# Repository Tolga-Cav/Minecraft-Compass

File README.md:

# Minecraft-Compass
3D printed functioning Minecraft Compass

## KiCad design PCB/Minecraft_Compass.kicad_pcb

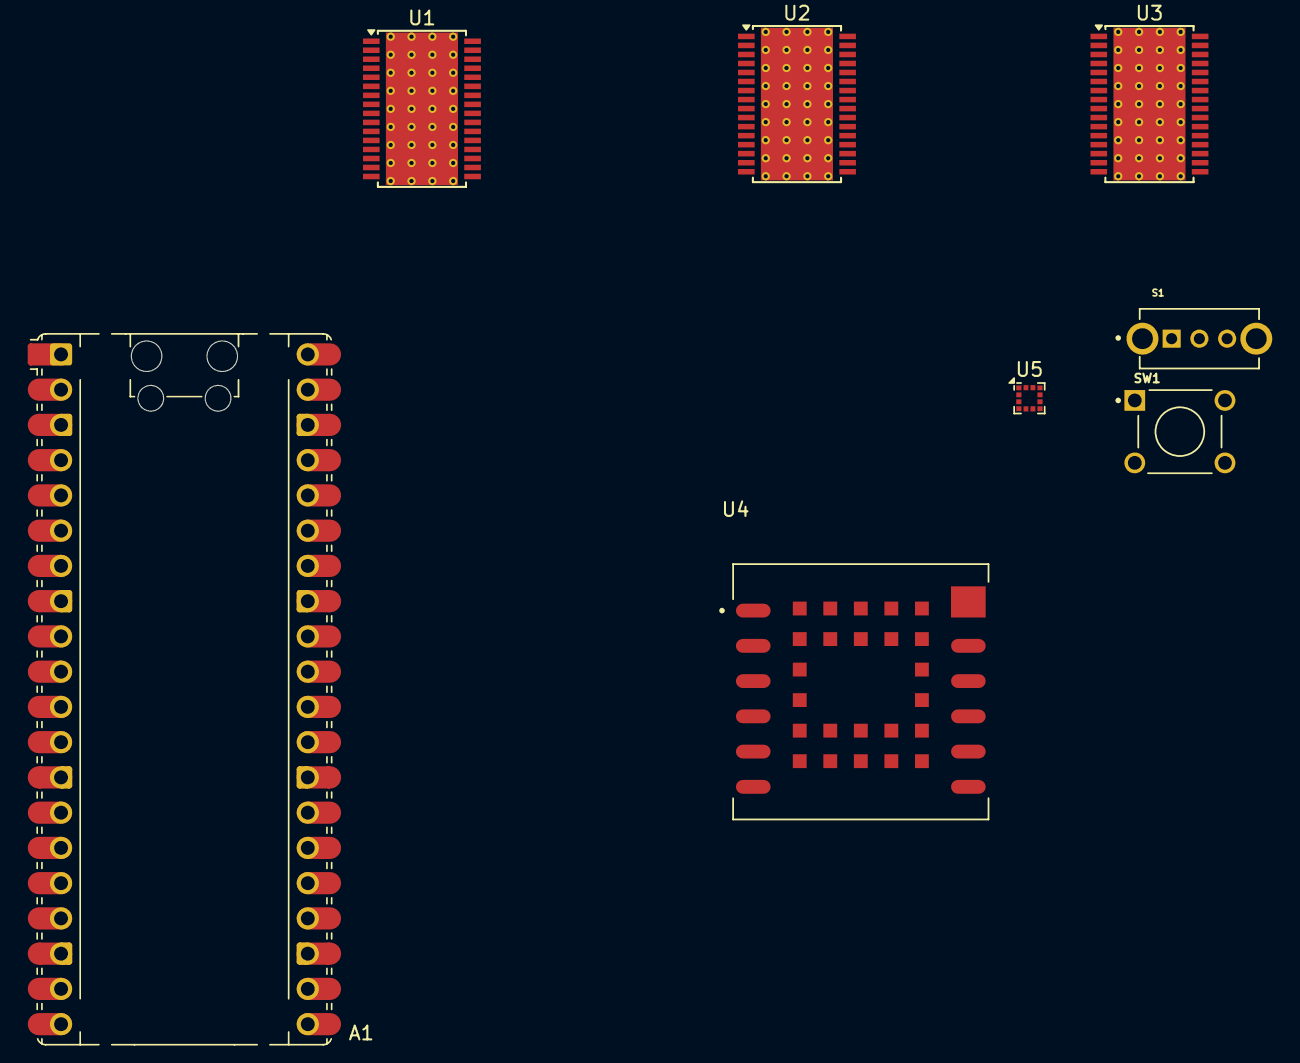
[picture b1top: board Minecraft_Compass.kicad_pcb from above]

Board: 2 copper layers, 8 parts (0 on the bottom side), 2 nets, no tracks yet.

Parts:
A1: RaspberryPi_Pico; RaspberryPi_Pico_Common_Unspecified
S1: OS102011MS2QN1; SW_OS102011MS2QN1
SW1: 1825910-6; SW_1825910-6-4
U1, U2, U3: TLC5947DAP; HTSSOP-32-1EP_6.1x11mm_P0.65mm_EP5.2x11mm_Mask4.11x4.36mm_T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
U4: LC86G; XCVR_LC86G
U5: LIS3MDL; LGA-12_2x2mm_P0.5mm

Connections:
unnamed: A1.3 (GND), A1.8 (GND), A1.13 (GND), A1.18 (GND), A1.23 (GND), A1.28 (GND), A1.38 (GND)
unnamed: U5.2 (GND), U5.3 (GND), U5.12 (GND)

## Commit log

2026-01-26 Set Up CAD project
2026-02-02 Set up KiCad project and begin schematic
2026-03-01 Add datasheets for electrical components
2026-04-27 Update LED Setup
